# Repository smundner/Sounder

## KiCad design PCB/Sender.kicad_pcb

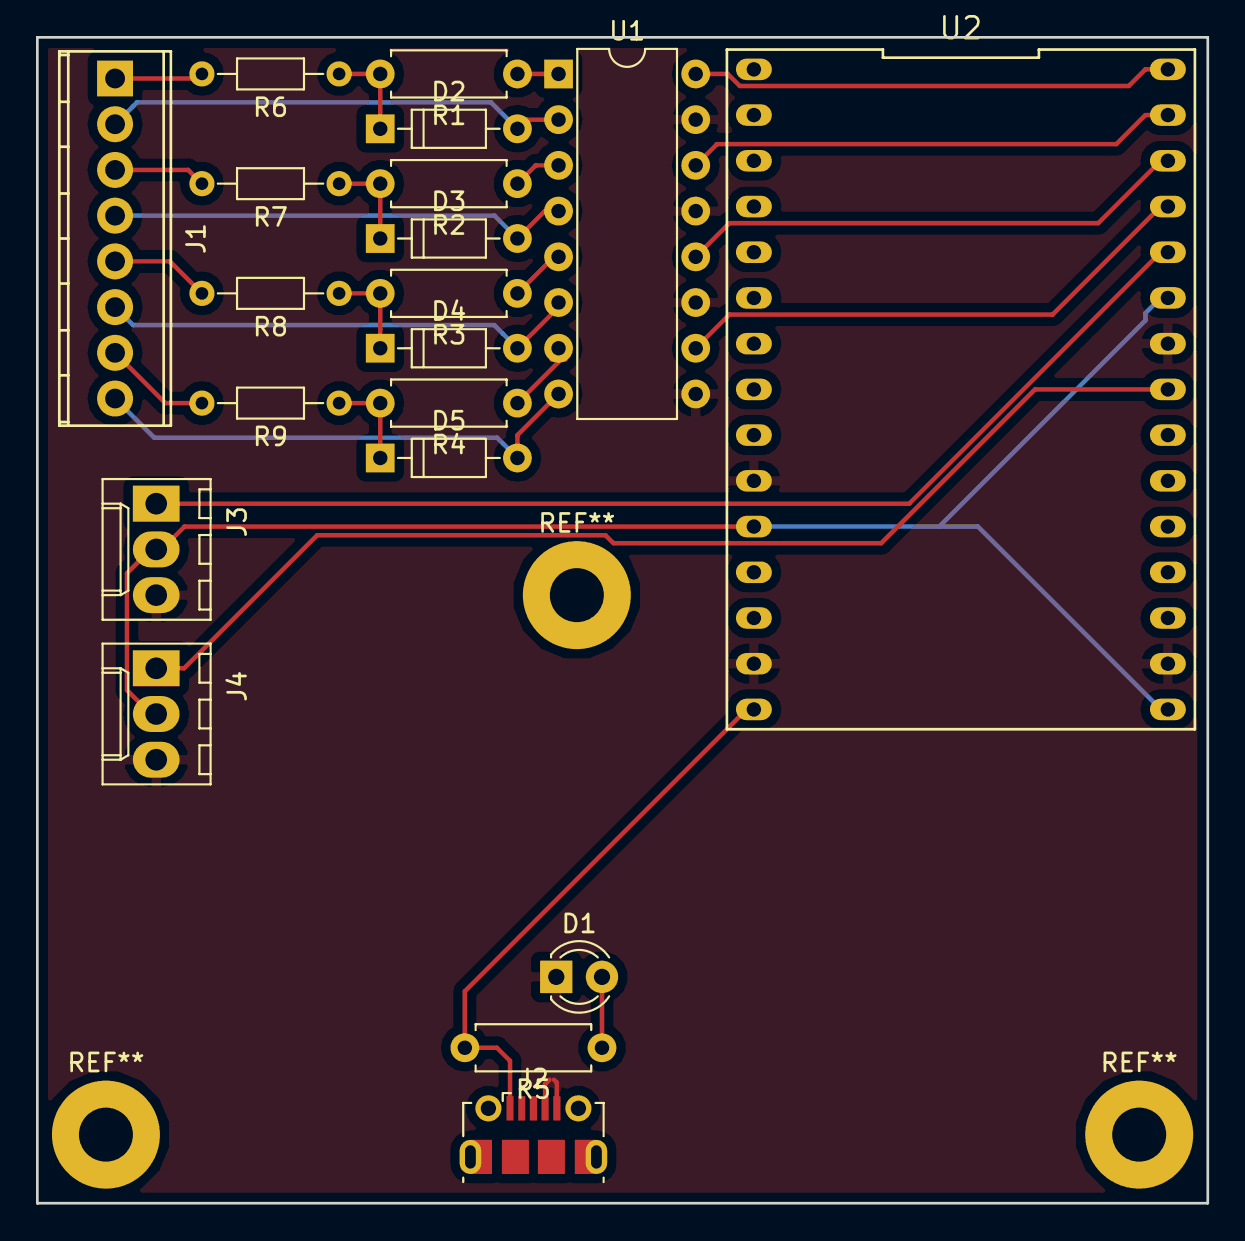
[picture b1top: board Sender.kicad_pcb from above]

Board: 2 copper layers, 65.0 x 64.8 mm, 20 parts (0 on the bottom side), 26 nets.

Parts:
D1: LED; LED_D3.0mm
D2, D3, D4, D5: D_Zener; D_DO-35_SOD27_P7.62mm_Horizontal
J1: Screw_Terminal_01x08; TerminalBlock_Pheonix_MPT-2.54mm_8pol
J2: USB_B; USB_Micro-B_Molex-105017-0001
J3, J4: Conn_01x03_Male; Molex_KK-6410-03_03x2.54mm_Straight
R1, R2, R3, R4, R5: R; R_Axial_DIN0207_L6.3mm_D2.5mm_P7.62mm_Horizontal
R6, R7, R8, R9: R; R_Axial_DIN0204_L3.6mm_D1.6mm_P7.62mm_Horizontal
U1: TLP291-4; DIP-16_W7.62mm
U2: NodeMCU1.0(ESP-12E); DIP-30_1_ELL

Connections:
+3V3: J3.2, J4.2, U2.11, U2.16, U2.25
+5V: J2.1, R5.2, U2.15
/D0: U1.16, U2.30
/D1: U1.14, U2.29
/D2: U1.12, U2.28
/D3: U1.10, U2.27
/D4: J3.1, U2.26
/D5: J4.1, U2.23
GND: D1.1, J2.4, J2.5, J3.3, J4.3, U1.9, U1.11, U1.13, U1.15, U2.10, U2.14, U2.17, U2.24
unnamed: D1.2, R5.1
unnamed: D2.1, R1.2, R6.1
unnamed: D2.2, J1.2, U1.2
unnamed: D3.1, R2.2, R7.1
unnamed: D3.2, J1.4, U1.4
unnamed: D4.1, R3.2, R8.1
unnamed: D4.2, J1.6, U1.6
unnamed: D5.1, R4.2, R9.1
unnamed: D5.2, J1.8, U1.8
unnamed: J1.1, R6.2
unnamed: J1.3, R7.2
unnamed: J1.5, R8.2
unnamed: J1.7, R9.2
unnamed: R1.1, U1.1
unnamed: R2.1, U1.3
unnamed: R3.1, U1.5
unnamed: R4.1, U1.7

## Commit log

2018-07-03 add android app
2018-07-03 auflistung ssid
2018-07-08 create auto login
2018-08-07 Platine upgrade software change
    Platine wurde angepasst mit einer schutzbeschaltung für die eingänge.
    Sende program wurde eine auswertungder eingänge eingefügt
    App wurde weiter entwickelt. es wird jetzt das wlan netz zum senden genutzt
2018-08-22 Gehäuse hinzugefügt
2018-08-23 Test input
2018-08-24 we sicherung
2018-09-05 conver android project
